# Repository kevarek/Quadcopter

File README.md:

# Quadcopter
Another quadcopter project, custom hardware with STM32F303 and firmware based on Keil RTX

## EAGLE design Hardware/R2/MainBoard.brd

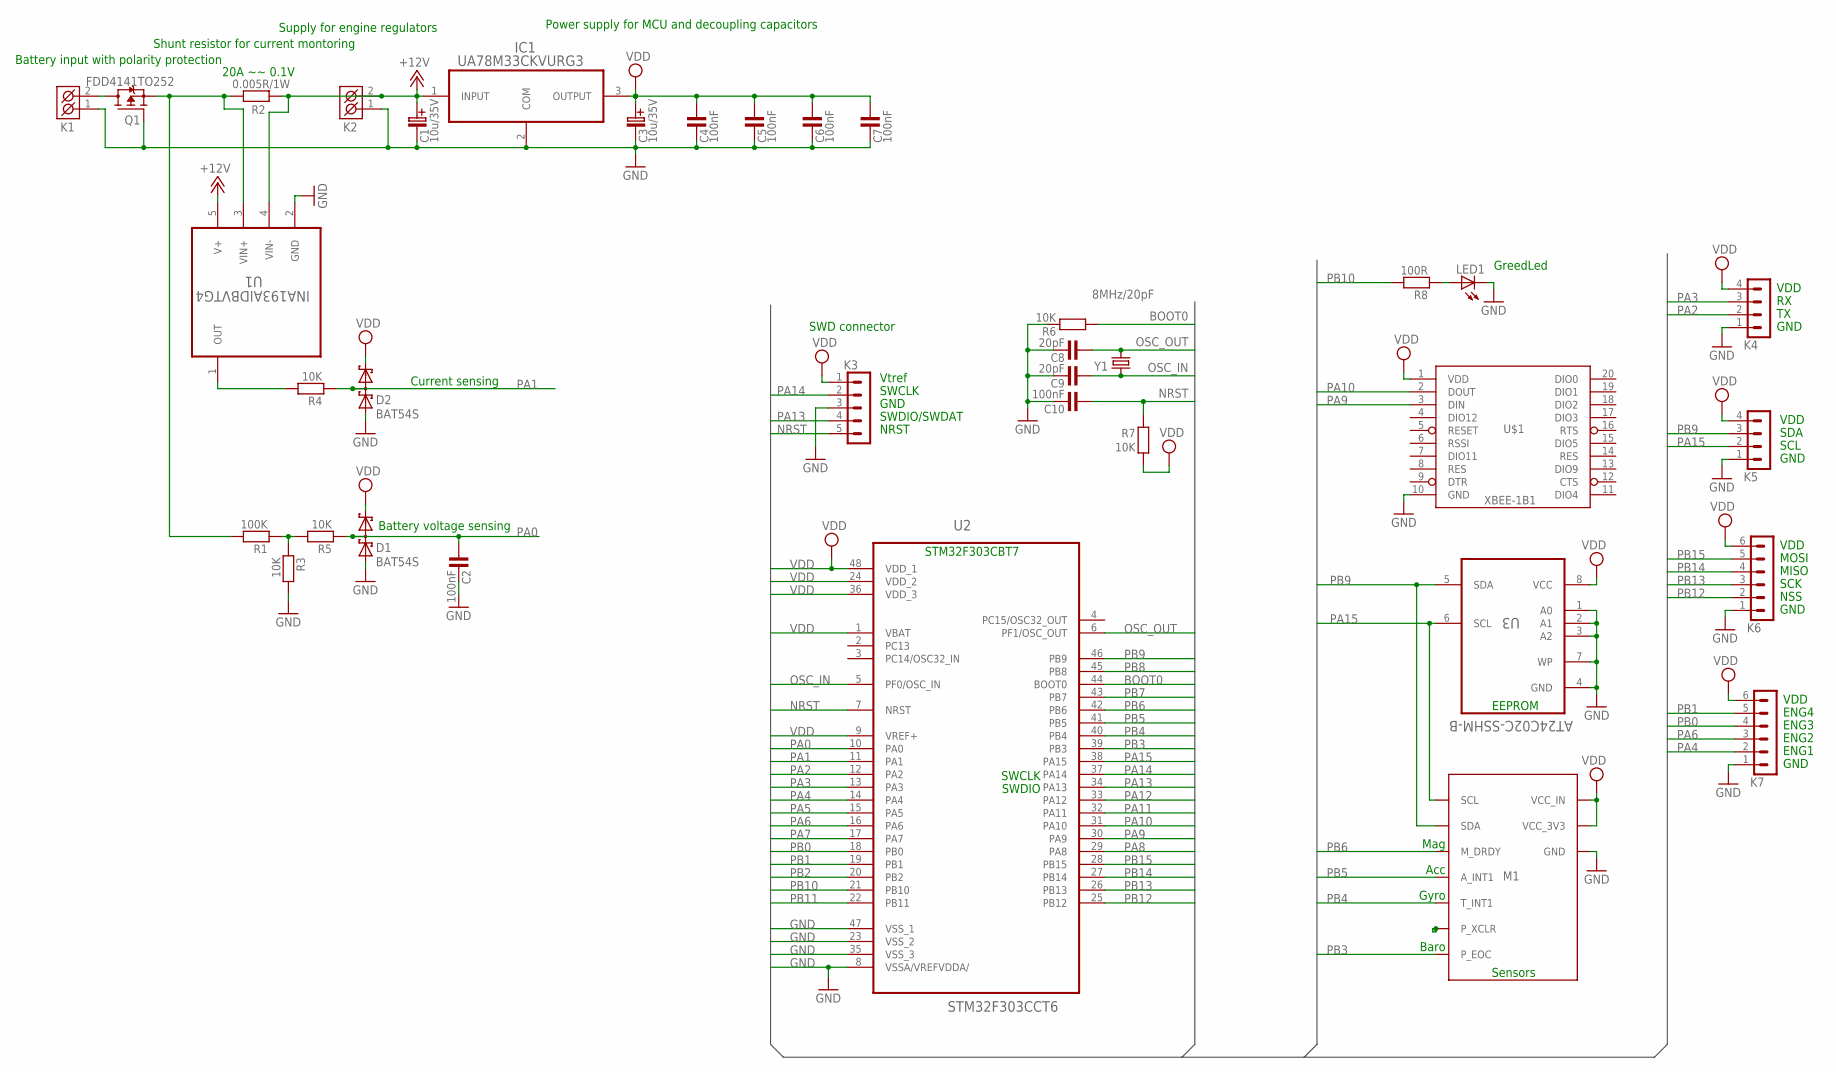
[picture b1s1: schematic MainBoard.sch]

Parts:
C1, C3: 10u/35V; C-EL_2,5
C2, C4, C5, C6, C7, C10: 100nF; 1206
C8, C9: 20pF; 1206
D1, D2: BAT54S; SOT23
IC1: UA78M33CKVURG3; TO285P991X230-3N
K1, K2: ARK500/2
K3: PSH02-05P
K4, K5: PSH02-04P
K6, K7: PSH02-06P
LED1: LED_E; LED_1206
M1: GY-80_DEV; GY-80_PAC
Q1: FDD4141TO252; TO252
R1: 100K; 1206
R2: 0.005R/1W; R-12,7
R3, R4, R5, R6, R7: 10K; 1206
R8: 100R; 1206
U1: INA193AIDBVTG4; SOT95P280X145-5N
U2: STM32F303CCT6; QFP50P900X900X160-48N
U3: AT24C02C-SSHM-B; SOIC127P600X175-8N
U$1: XBEE-1B1; XBEE-1
Y1: 8MHz/20pF; HC49UP

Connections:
+12V: C1.C+ (C_EL+), IC1.1 (INPUT), K2.2 (K2), R2.1, U1.4 (VIN-), U1.5 (V+)
BOOT0: R6.2, U2.44 (BOOT0)
GND: C1.C- (C_EL-), C2.2, C3.C- (C_EL-), C4.2, C5.2, C6.2, C7.2, C8.2, C9.2, C10.2, D1.1 (A1), D2.1 (A1), IC1.2 (COM), K1.1 (K1), K2.1 (K1), K3.3, K4.1, K5.1, K6.1, K7.1, LED1.C, M1.GND, Q1.1 (G), R3.2, R6.1, U1.2 (GND), U2.8 (VSSA/VREFVDDA/), U2.23 (VSS_2), U2.35 (VSS_3), U2.47 (VSS_1), U3.1 (A0), U3.2 (A1), U3.3 (A2), U3.4 (GND), U3.7 (WP), U$1.10 (GND)
unnamed: R4.2, U1.1 (OUT)
unnamed: Q1.2 (S), R1.2, R2.2, U1.3 (VIN+)
unnamed: K1.2 (K2), Q1.3 (D)
unnamed: R1.1, R3.1, R5.2
unnamed: LED1.A, R8.1
NRST: C10.1, K3.5, R7.2, U2.7 (NRST)
OSC_IN: C9.1, U2.5 (PF0/OSC_IN), Y1.1
OSC_OUT: C8.1, U2.6 (PF1/OSC_OUT), Y1.2
PA0: C2.1, D1.3 (C1A2), R5.1, U2.10 (PA0)
PA1: D2.3 (C1A2), R4.1, U2.11 (PA1)
PA2: K4.2, U2.12 (PA2)
PA3: K4.3, U2.13 (PA3)
PA4: K7.2, U2.14 (PA4)
PA5: U2.15 (PA5)
PA6: K7.3, U2.16 (PA6)
PA7: U2.17 (PA7)
PA8: U2.29 (PA8)
PA9: U2.30 (PA9), U$1.3 (DIN)
PA10: U2.31 (PA10), U$1.2 (DOUT)
PA11: U2.32 (PA11)
PA12: U2.33 (PA12)
PA13: K3.4, U2.34 (PA13)
PA14: K3.2, U2.37 (PA14)
PA15: K5.2, M1.SCL, U2.38 (PA15), U3.6 (SCL)
PB0: K7.4, U2.18 (PB0)
PB1: K7.5, U2.19 (PB1)
PB2: U2.20 (PB2)
PB3: M1.P_EOC, U2.39 (PB3)
PB4: M1.T_INT1, U2.40 (PB4)
PB5: M1.A_INT1, U2.41 (PB5)
PB6: M1.M_DRDY, U2.42 (PB6)
PB7: U2.43 (PB7)
PB8: U2.45 (PB8)
PB9: K5.3, M1.SDA, U2.46 (PB9), U3.5 (SDA)
PB10: R8.2, U2.21 (PB10)
PB11: U2.22 (PB11)
PB12: K6.2, U2.25 (PB12)
PB13: K6.3, U2.26 (PB13)
PB14: K6.4, U2.27 (PB14)
PB15: K6.5, U2.28 (PB15)
VDD: C3.C+ (C_EL+), C4.1, C5.1, C6.1, C7.1, D1.2 (C2), D2.2 (C2), IC1.3 (OUTPUT), K3.1, K4.4, K5.4, K6.6, K7.6, M1.VCC_3V3, M1.VCC_IN, R7.1, U2.1 (VBAT), U2.9 (VREF+), U2.24 (VDD_2), U2.36 (VDD_3), U2.48 (VDD_1), U3.8 (VCC), U$1.1 (VDD)

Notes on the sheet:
Power supply for MCU and decoupling capacitors
EEPROM
Sensors
Mag
Acc
Gyro
Battery input with polarity protection
Supply for engine regulators
Baro
20A ~~ 0.1V
Shunt resistor for current montoring
STM32F303CBT7
SWDIO
SWCLK
GND
SWDIO/SWDAT
NRST
Vtref
SWD connector
GreedLed
Current sensing
Battery voltage sensing
VDD
SDA
SCL
MOSI
MISO
SCK
NSS
ENG1
ENG2
ENG3
ENG4

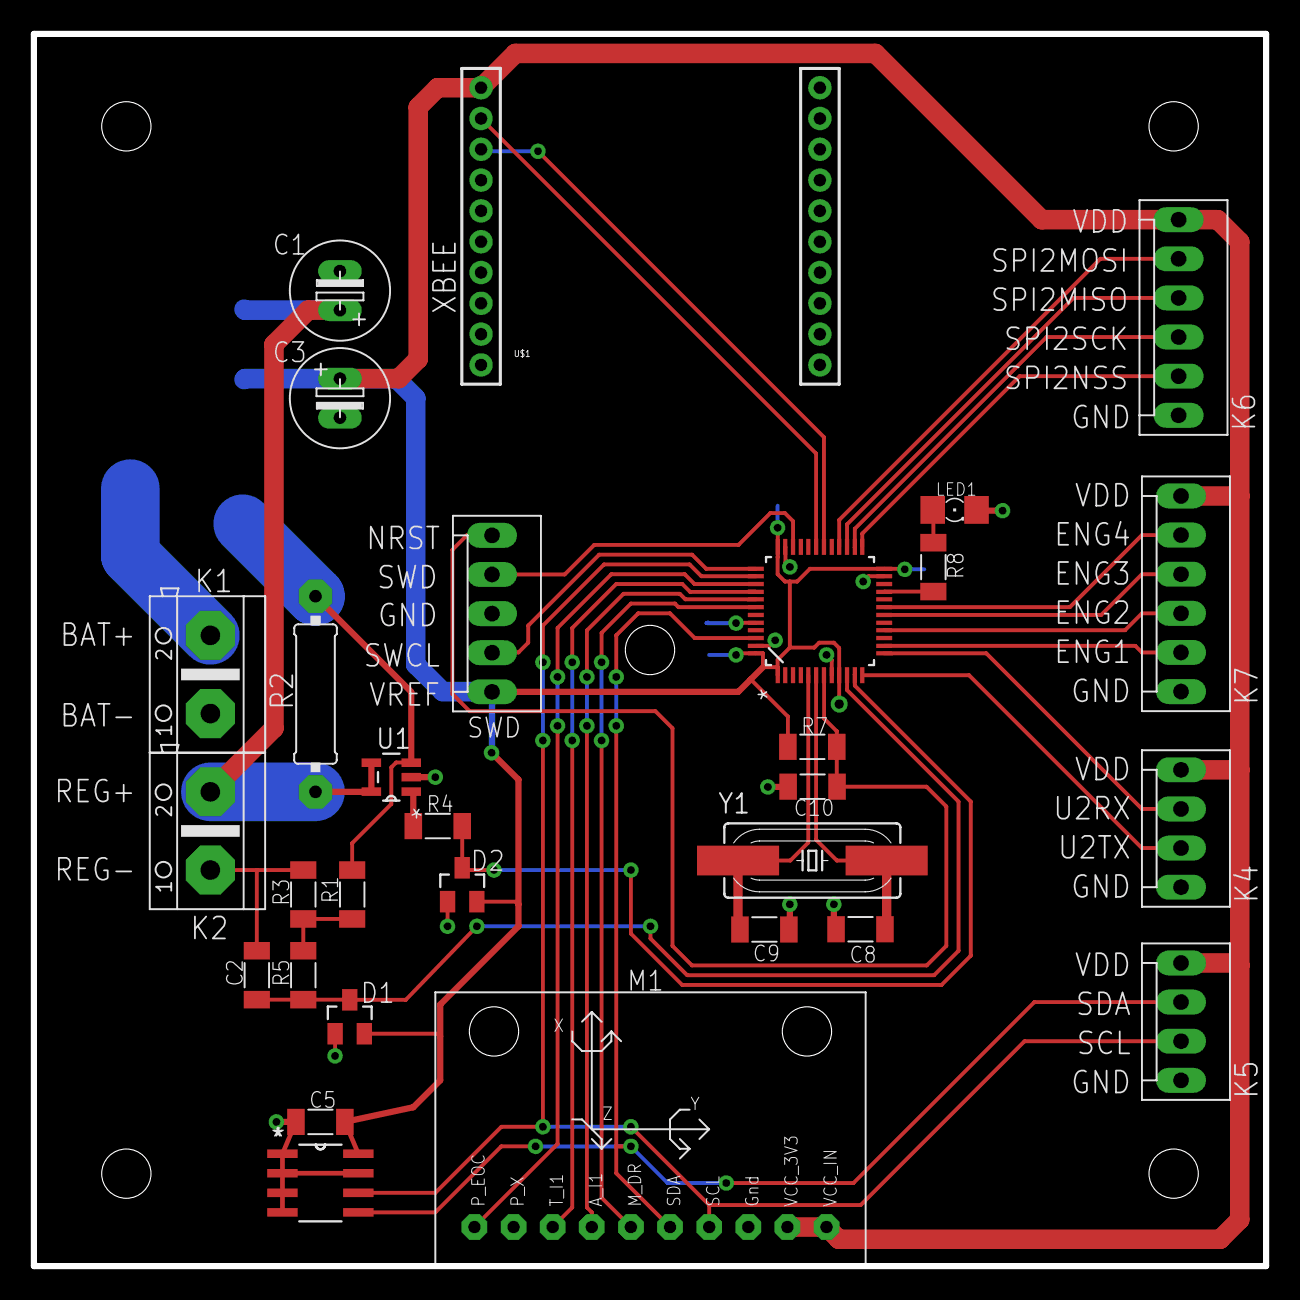
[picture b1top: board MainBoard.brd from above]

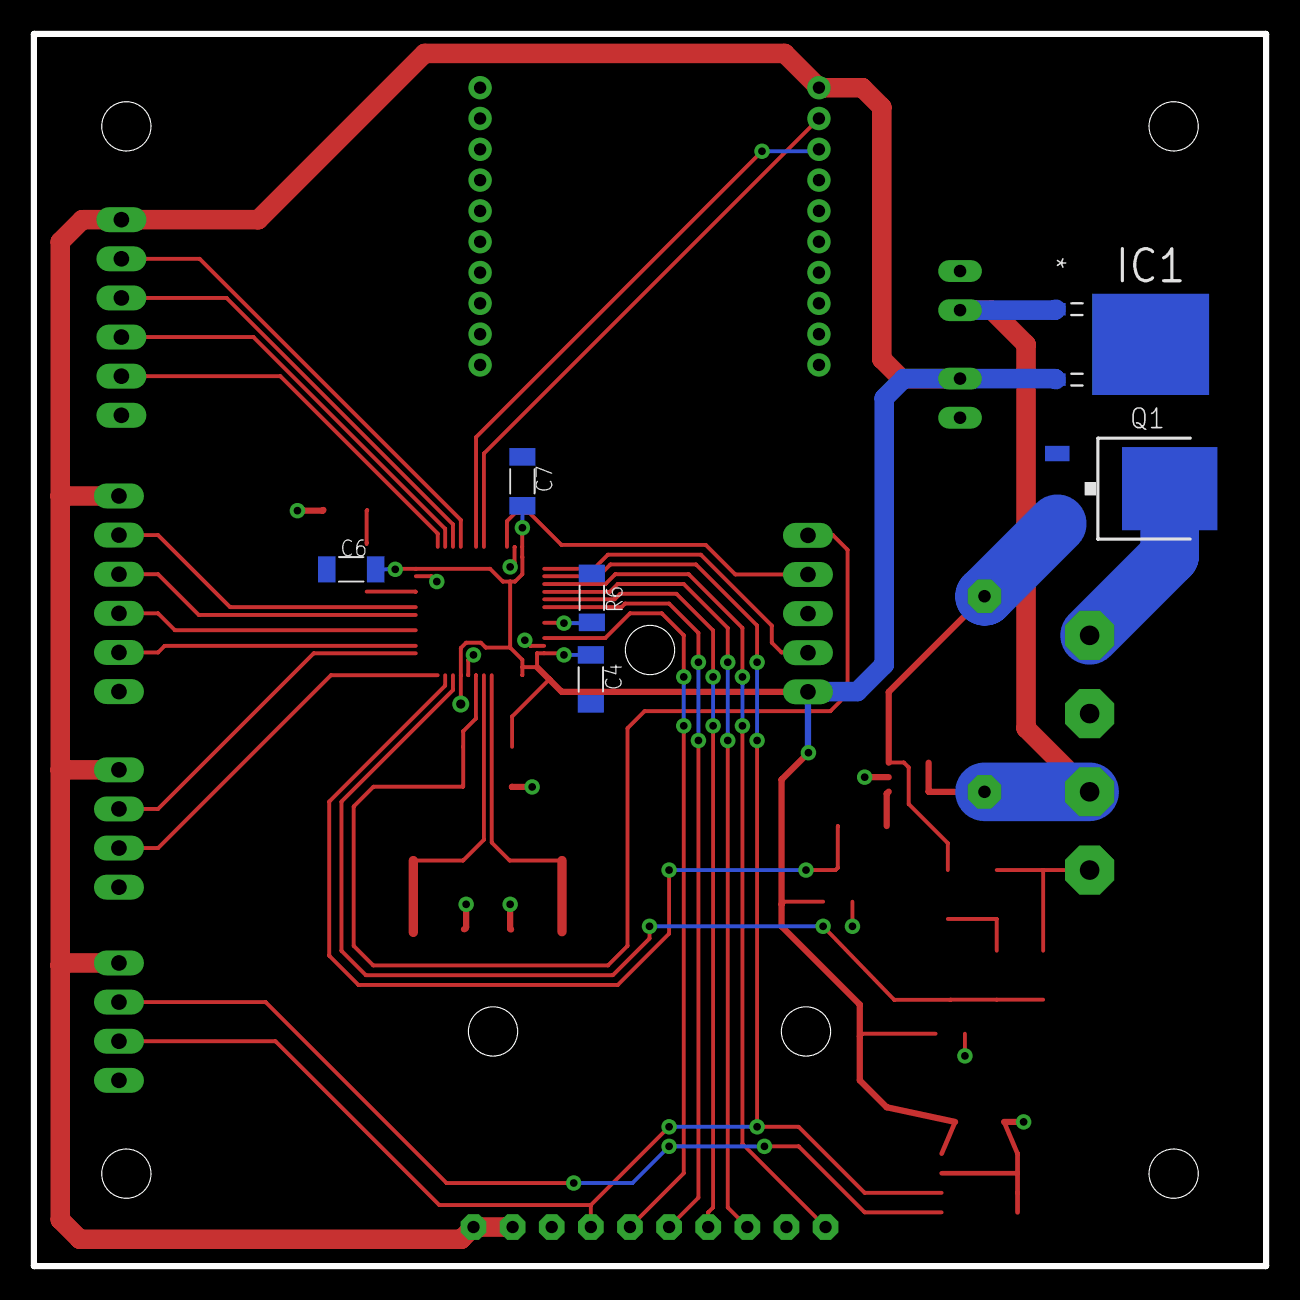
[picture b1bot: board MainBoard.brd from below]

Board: 2 copper layers, 80.0 x 80.0 mm, 36 parts (6 on the bottom side), 35 nets.

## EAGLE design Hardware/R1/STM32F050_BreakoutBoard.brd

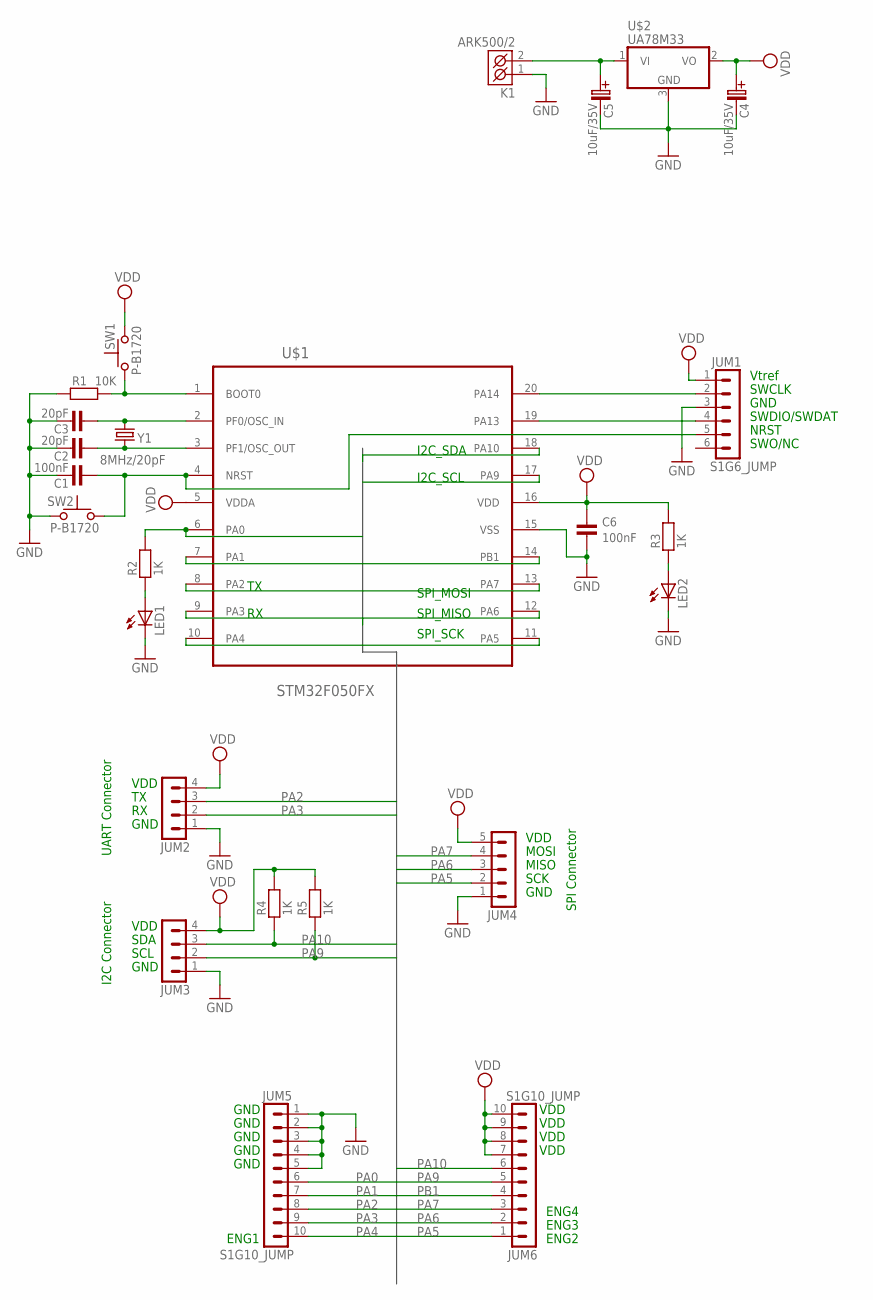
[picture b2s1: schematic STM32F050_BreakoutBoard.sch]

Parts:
C1, C6: 100nF; 1206
C2, C3: 20pF; 1206
C4, C5: 10uF/35V; C-EL_2,5
JUM1: S1G6_JUMP; S1G6_JUM
JUM2, JUM3: S1G4_JUMP; S1G4_JUM
JUM4: S1G5_JUMP; S1G5_JUM
JUM5, JUM6: S1G10_JUMP; S1G10_JU
K1: ARK500/2
LED1, LED2: LED_E; LED_1206
R1: 10K; 1206
R2, R3, R4, R5: 1K; 1206
SW1, SW2: P-B1720
U$1: STM32F050FX; TSSOP20
U$2: UA78M33; TO252
Y1: 8MHz/20pF; HC49UP

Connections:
GND: C1.2, C2.2, C3.2, C4.C- (C_EL-), C5.C- (C_EL-), C6.2, JUM1.3, JUM2.1, JUM3.1, JUM4.1, JUM5.1, JUM5.2, JUM5.3, JUM5.4, JUM5.5, K1.1 (K1), LED1.C, LED2.C, R1.1, SW2.2, U$1.15 (VSS), U$2.3 (GND)
unnamed: C3.1, U$1.2 (PF0/OSC_IN), Y1.2
unnamed: C2.1, U$1.3 (PF1/OSC_OUT), Y1.1
unnamed: R1.2, SW1.1, U$1.1 (BOOT0)
unnamed: C5.C+ (C_EL+), K1.2 (K2), U$2.1 (VI)
unnamed: LED1.A, R2.1
unnamed: JUM1.2, U$1.20 (PA14)
unnamed: JUM1.4, U$1.19 (PA13)
unnamed: C1.1, JUM1.5, SW2.1, U$1.4 (NRST)
unnamed: LED2.A, R3.1
PA0: JUM5.6, R2.2, U$1.6 (PA0)
PA1: JUM5.7, U$1.7 (PA1)
PA2: JUM2.3, JUM5.8, U$1.8 (PA2)
PA3: JUM2.2, JUM5.9, U$1.9 (PA3)
PA4: JUM5.10, U$1.10 (PA4)
PA5: JUM4.2, JUM6.1, U$1.11 (PA5)
PA6: JUM4.3, JUM6.2, U$1.12 (PA6)
PA7: JUM4.4, JUM6.3, U$1.13 (PA7)
PA9: JUM3.2, JUM6.5, R5.1, U$1.17 (PA9)
PA10: JUM3.3, JUM6.6, R4.1, U$1.18 (PA10)
PB1: JUM6.4, U$1.14 (PB1)
VDD: C4.C+ (C_EL+), C6.1, JUM1.1, JUM2.4, JUM3.4, JUM4.5, JUM6.7, JUM6.8, JUM6.9, JUM6.10, R3.2, R4.2, R5.2, SW1.2, U$1.5 (VDDA), U$1.16 (VDD), U$2.2 (VO)

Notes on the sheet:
SWCLK
GND
SWDIO/SWDAT
NRST
SWO/NC
SPI_SCK
SPI_MISO
SPI_MOSI
I2C_SCL
I2C_SDA
VDD
SDA
SCL
MOSI
MISO
SCK
ENG1
ENG2
ENG3
ENG4
Vtref
SPI Connector
UART Connector
I2C Connector

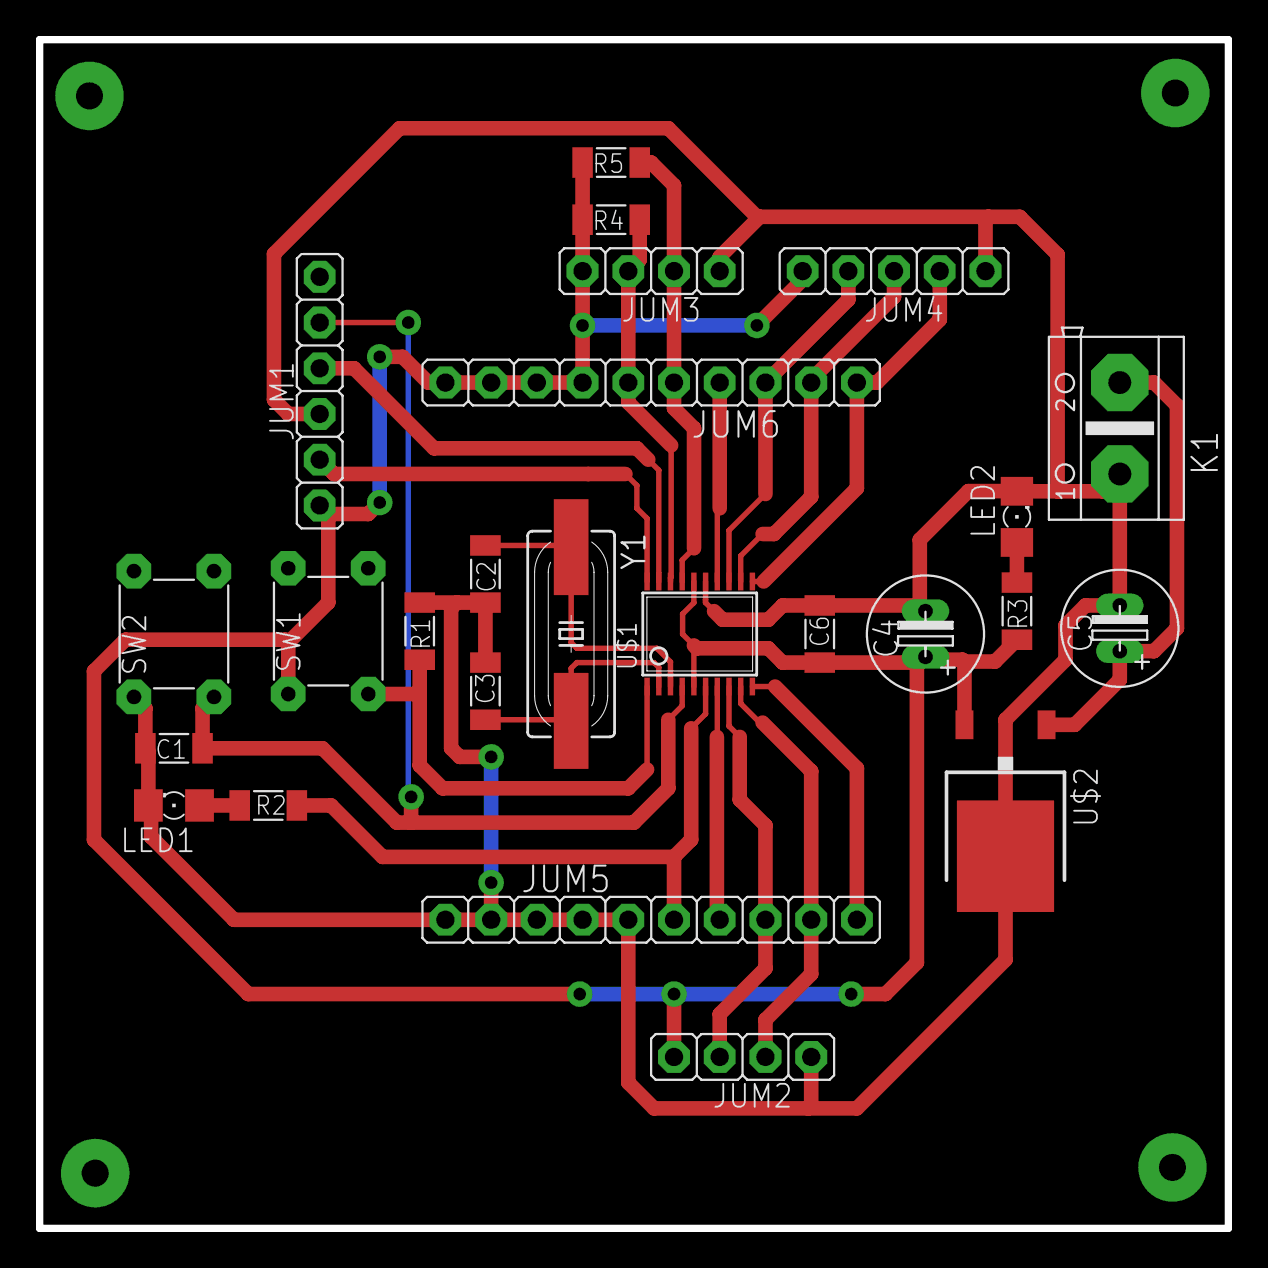
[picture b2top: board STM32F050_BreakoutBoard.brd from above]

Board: 2 copper layers, 66.0 x 66.0 mm, 25 parts (0 on the bottom side), 22 nets.

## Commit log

2016-05-15 Initial commit
    Repository moved from SVN based to github.

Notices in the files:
parts and their libraries:
SparkFun: Licensing: CC v3.0 Share-Alike You are welcome to use this library for commercial purposes.
Copyright (C) PaJa 2011
Copyright (C) PaJa 2001-2011
